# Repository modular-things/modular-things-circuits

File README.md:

# modular-things-circuits

Hardware repo for [modular-things](https://github.com/modular-things/modular-things/) custom circuits. Each folder includes a shematic image, board image, and relevant design files in a Fusion 360 Archive. 

`/samd21` contains the OG modular-things circuits based on the ATSAMD21E18A  

`/xiao` contains newer designs based on the seeed xiao development boards, in particular the RP2040 version  

`/backpacks` contain modular PHY add-ons, in development  

`/jewel` contains the stub of a usb-power-delivery based xiao-like module we are ~ planning  

To design a new board, you can start with the [base design for samd21s](samd21/base) or the [base design for the xiao platform](xiao/base). 

Note that it is also possible to virtualize *almost any existing arduino project* as a modular-thing - these circuits are just a cohesive, demonstrative set.

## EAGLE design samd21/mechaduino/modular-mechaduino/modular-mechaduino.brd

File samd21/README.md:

## atsamd21 based modular-things circuits

---

| accelerometer | |
| --- | --- |
|  |  |

| part | count | info ? |
| --- | --- | --- |
| ATSAMD21 | 1 | uc |
| JTAG 10-pin | 1 |
| VREG | 1 | 
| LSM6DSO Accelerometer | 1 |
| 0R 1206 | 1 |
| 1k 1206 | 1 |
| 2k2 1206 | 2 |
| 10k 1206 | 1 |
| 0.1uF 1206 | 2 |
| 1uF 1206 | 2 |
| 10uF 1206 | 2 |

---

| breadboard | |
| --- | --- |
|  |  |

| part | count | info ? |
| --- | --- | --- |
| ATSAMD21 | 1 | uc |
| JTAG 10-pin | 1 |
| VREG (big) | 1 | 
| 0R 1206 | 1 |
| 10k 1206 | 1 |
| 1uF 1206 | 2 |
| 10uF 1206 | 2 |

---

| capacitive | |
| --- | --- |
|  |  |

| part | count | info ? |
| --- | --- | --- |
| ATSAMD21 | 1 | uc |
| JTAG 10-pin | 1 |
| VREG | 1 | 
| 0R 1206 | 1 |
| 1k 1206 | 3 |
| 10k 1206 | 1 |
| 1uF 1206 | 2 |
| 10uF 1206 | 2 |

---

| low-fet | |
| --- | --- |
|  |  |

| part | count | info ? |
| --- | --- | --- |
| ATSAMD21 | 1 | uc |
| JTAG 10-pin | 1 |
| VREG | 1 | 
| NMOS | 1 |
| 2x3 SMT Header | 1 |
| 2x4 SMT Header | 1 |
| 0R 1206 | 2 |
| 1k 1206 | 2 |
| 10k 1206 | 1 |
| 1uF 1206 | 2 |
| 10uF 1206 | 2 |

---

| oled | |
| --- | --- |
|  |  |

`note: an early version of these circuits need SCL and SDA to be flipped in between the board and the OLED module`

| part | count | info ? |
| --- | --- | --- |
| ATSAMD21 | 1 | uc |
| JTAG 10-pin | 1 |
| VREG | 1 | 
| OLED Module | 1 |
| 0R 1206 | 1 |
| 4.99k 1206 | 2 |
| 10k 1206 | 1 |
| 1uF 1206 | 2 |
| 10uF 1206 | 2 |

---

| potentiometer | |
| --- | --- |
|  |  |

| part | count | info ? |
| --- | --- | --- |
| ATSAMD21 | 1 | uc |
| JTAG 10-pin | 1 |
| VREG | 1 | 
| POTS | 2 |
| 0R 1206 | 1 |
| 10k 1206 | 1 |
| 1uF 1206 | 2 |
| 10uF 1206 | 2 |

---

| rgbb | |
| --- | --- |
|  |  |

| part | count | info ? |
| --- | --- | --- |
| ATSAMD21 | 1 | uc |
| JTAG 10-pin | 1 |
| VREG | 1 | 
| RGB LED | 1 |
| SWTCH | 1 |
| 1x3 SMT Header | 1 |
| 0R 1206 | 1 |
| 1k 1206 | 3 |
| 10k 1206 | 2 |
| 1uF 1206 | 2 |
| 10uF 1206 | 2 |

---

| servo | |
| --- | --- |
|  |  |

| part | count | info ? |
| --- | --- | --- |
| ATSAMD21 | 1 | uc |
| JTAG 10-pin | 1 |
| VREG | 1 | 
| 1x3 SMT Header | 1 |
| 0R 1206 | 1 |
| 10k 1206 | 1 |
| 1uF 1206 | 1 |
| 10uF 1206 | 3 |

---

| stepper-hbridge | |
| --- | --- |
|  |  |

| part | count | info ? |
| --- | --- | --- |
| ATSAMD21 | 1 | uc |
| JTAG 10-pin | 1 |
| VREG | 1 | 
| H-Bridge | 2 |
| 2x3 SMT Header | 1 |
| 0R 1206 | 2 |
| 120R | 2 |
| Shunt | 2 | use ~ 300mOhm, we think |
| 10k 1206 | 1 |
| 0.1uF 1206 | 2 |
| 1uF 1206 | 4 |
| 10uF 1206 | 4 |

---

| sneaky mechaduino clone | |
| --- | --- |
|  |  |

In the style of the xiao boards (hole spacing / sizewise / PHY breakout wise) but w/ xiao! 

| part | count | info ? |
| --- | --- | --- |
| ATSAMD21 | 1 | uc |
| JTAG 10-pin | 1 |
| VREG | 1 | 
| H-Bridge | 2 |
| Shunt | 2 | use ~ 300mOhm, we think |
| 120R | 2 |
| 5k1 1206 | 2 |
| 10k 1206 | 1 |
| 0.1uF 1206 | 3 |
| 1uF 1206 | 4 |
| 10uF 1206 | 4 |

---

| time-of-flight | |
| --- | --- |
|  |  |

| part | count | info ? |
| --- | --- | --- |
| ATSAMD21 | 1 | uc |
| JTAG 10-pin | 1 |
| VREG | 1 | 
| VL53 TOF | 1 |
| 0R 1206 | 1 |
| 4.99k 1206 | 2 |
| 10k 1206 | 1 |
| 0.1uF 1206 | 1 |
| 1uF 1206 | 2 |
| 10uF 1206 | 2 |

---

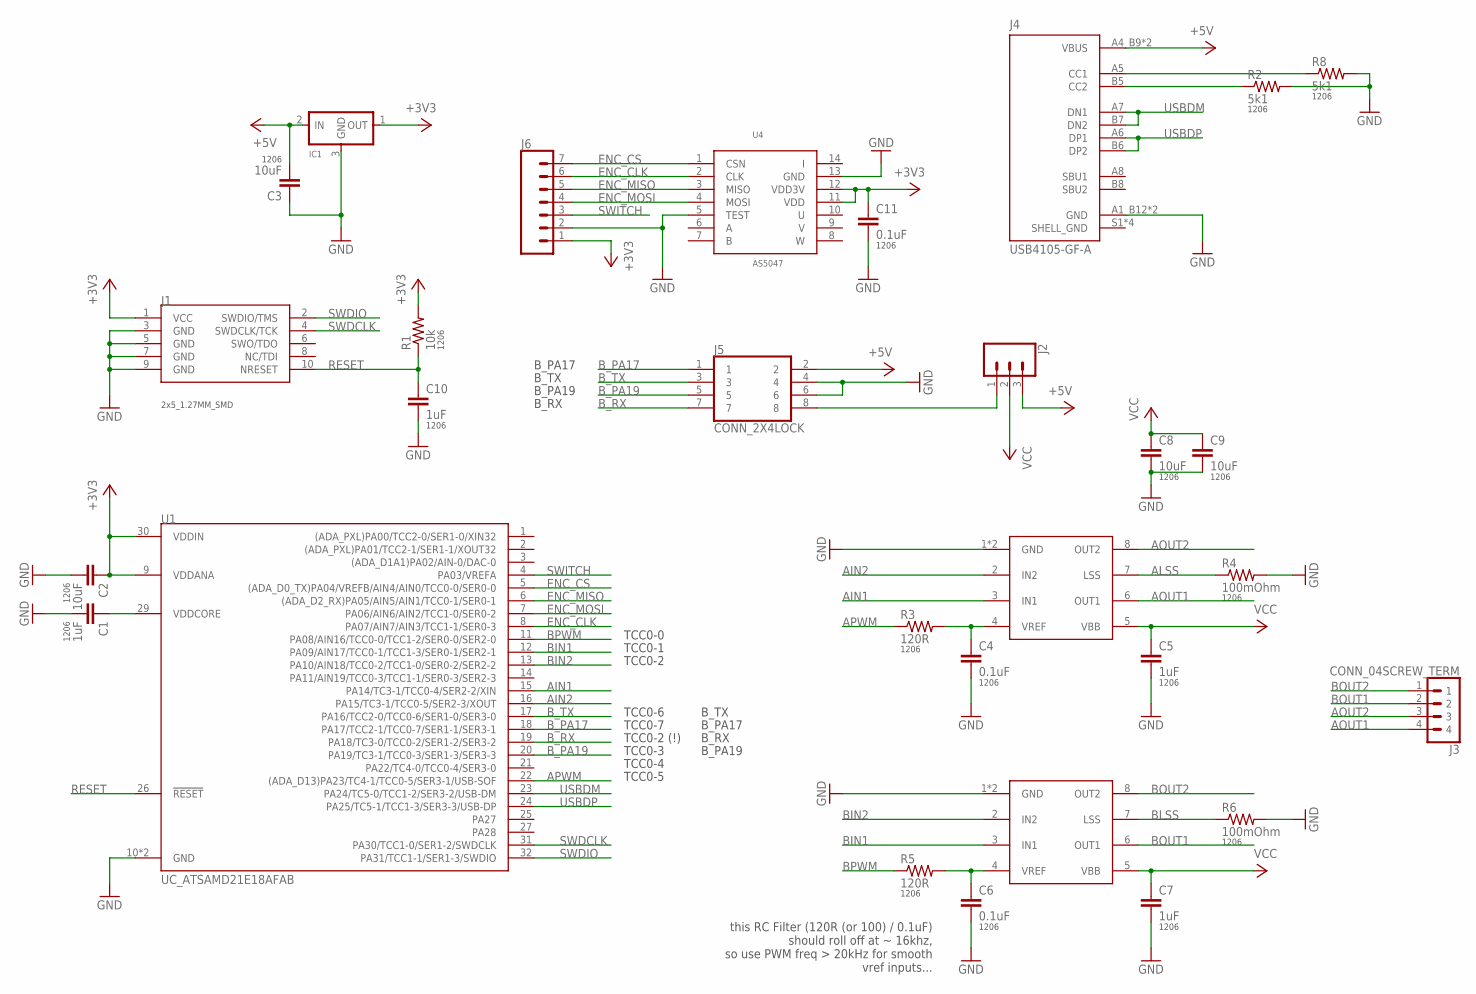
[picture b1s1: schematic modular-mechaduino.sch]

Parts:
C1, C5, C7, C10: 1uF; 1206
C2, C3, C8, C9: 10uF; 1206
C4, C6, C11: 0.1uF; 1206
IC1: VR_REGULATOR-SOT23SOT23; SOT23
J1: CONN_05X2_ARM_DEBUGSMD; 2X5_1.27MM_SMD
J2: CONN_03LOCK_NO_SILK; 1X03_LOCK_NO_SILK
J3: CONN_04SCREW_TERM; 1X04_SCREW-TERM
J4: USB4105-GF-A; GCT_USB4105-GF-A
J5: CONN_2X4LOCK; 2X4-LOCK
J6: CONN_07NO_SILK; 1X07_NO_SILK
R1: 10k; 1206
R2, R8: 5k1; 1206
R3, R5: 120R; 1206
R4, R6: 100mOhm; 1206
U1: UC_ATSAMD21E18AFAB; TQFP-32-FAB
U2, U3: A4950; SOIC8_PAD
U4: AS5047; TSSOP14

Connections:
+3V3: C2.1, C11.1, IC1.1 (OUT), J1.1 (VCC), J6.1, R1.2, U1.9 (VDDANA), U1.30 (VDDIN), U4.11 (VDD), U4.12 (VDD3V)
+5V: C3.2, IC1.2 (IN), J2.3, J4.A4_B9 (VBUS), J4.B4_A9 (VBUS), J5.2
AIN1: U1.15 (PA14/TC3-1/TCC0-4/SER2-2/XIN), U2.3 (IN1)
AIN2: U1.16 (PA15/TC3-1/TCC0-5/SER2-3/XOUT), U2.2 (IN2)
ALSS: R4.1, U2.7 (LSS)
AOUT1: J3.4, U2.6 (OUT1)
AOUT2: J3.3, U2.8 (OUT2)
APWM: R3.1, U1.22 ((ADA_D13)PA23/TC4-1/TCC0-5/SER3-1/USB-S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)
BIN1: U1.12 (PA09/AIN17/TCC0-1/TCC1-3/SER0-1/SER2-1), U3.3 (IN1)
BIN2: U1.13 (PA10/AIN18/TCC0-2/TCC1-0/SER0-2/SER2-2), U3.2 (IN2)
BLSS: R6.1, U3.7 (LSS)
BOUT1: J3.2, U3.6 (OUT1)
BOUT2: J3.1, U3.8 (OUT2)
BPWM: R5.1, U1.11 (PA08/AIN16/TCC0-0/TCC1-2/SER0-0/SER2-0)
B_PA17: J5.1, U1.18 (PA17/TCC2-1/TCC0-7/SER1-1/SER3-1)
B_PA19: J5.5, U1.20 (PA19/TC3-1/TCC0-3/SER1-3/SER3-3)
B_RX: J5.7, U1.19 (PA18/TC3-0/TCC0-2/SER1-2/SER3-2)
B_TX: J5.3, U1.17 (PA16/TCC2-0/TCC0-6/SER1-0/SER3-0)
ENC_CLK: J6.6, U1.8 (PA07/AIN7/AIN3/TCC1-1/SER0-3), U4.2 (CLK)
ENC_CS: J6.7, U1.5 ((ADA_D0_TX)PA04/VREFB/AIN4/AIN0/TCC0-0/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), U4.1 (CSN)
ENC_MISO: J6.5, U1.6 ((ADA_D2_RX)PA05/AIN5/AIN1/TCC0-1/SER0-1), U4.3 (MISO)
ENC_MOSI: J6.4, U1.7 (PA06/AIN6/AIN2/TCC1-0/SER0-2), U4.4 (MOSI)
GND: C1.2, C2.2, C3.1, C4.2, C5.2, C6.2, C7.2, C8.2, C9.2, C10.2, C11.2, IC1.3 (GND), J1.3 (GND), J1.5 (GND), J1.7 (GND), J1.9 (GND), J4.A1_B12 (GND), J4.B1_A12 (GND), J5.4, J5.6, J6.2, R2.2, R4.2, R6.2, R8.2, U1.10 (GND), U1.28 (GND), U2.1 (GND), U2.P$1 (GND), U3.1 (GND), U3.P$1 (GND), U4.5 (TEST), U4.13 (GND)
unnamed: C1.1, U1.29 (VDDCORE)
unnamed: C4.1, R3.2, U2.4 (VREF)
unnamed: J4.B5 (CC2), R2.1
unnamed: J4.A5 (CC1), R8.1
unnamed: C6.1, R5.2, U3.4 (VREF)
unnamed: J2.1, J5.8
RESET: C10.1, J1.10 (NRESET), R1.1, U1.26 (!RESET)
SHELL_GND: J4.S1 (SHELL_GND), J4.S2 (SHELL_GND), J4.S3 (SHELL_GND), J4.S4 (SHELL_GND)
SWDCLK: J1.4 (SWDCLK/TCK), U1.31 (PA30/TCC1-0/SER1-2/SWDCLK)
SWDIO: J1.2 (SWDIO/TMS), U1.32 (PA31/TCC1-1/SER1-3/SWDIO)
SWITCH: J6.3, U1.4 (PA03/VREFA)
USBDM: J4.A7 (DN1), J4.B7 (DN2), U1.23 (PA24/TC5-0/TCC1-2/SER3-2/USB-DM)
USBDP: J4.A6 (DP1), J4.B6 (DP2), U1.24 (PA25/TC5-1/TCC1-3/SER3-3/USB-DP)
VCC: C5.1, C7.1, C8.1, C9.1, J2.2, U2.5 (VBB), U3.5 (VBB)

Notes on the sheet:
TCC0-0
TCC0-1
TCC0-2
TCC0-3
TCC0-4
TCC0-5
TCC0-2 (!)
TCC0-7
TCC0-6
this RC Filter (120R (or 100) / 0.1uF) should roll off at ~ 16khz, so use PWM freq > 20kHz for smooth vref inputs...
B_PA17
B_TX
B_PA19
B_RX

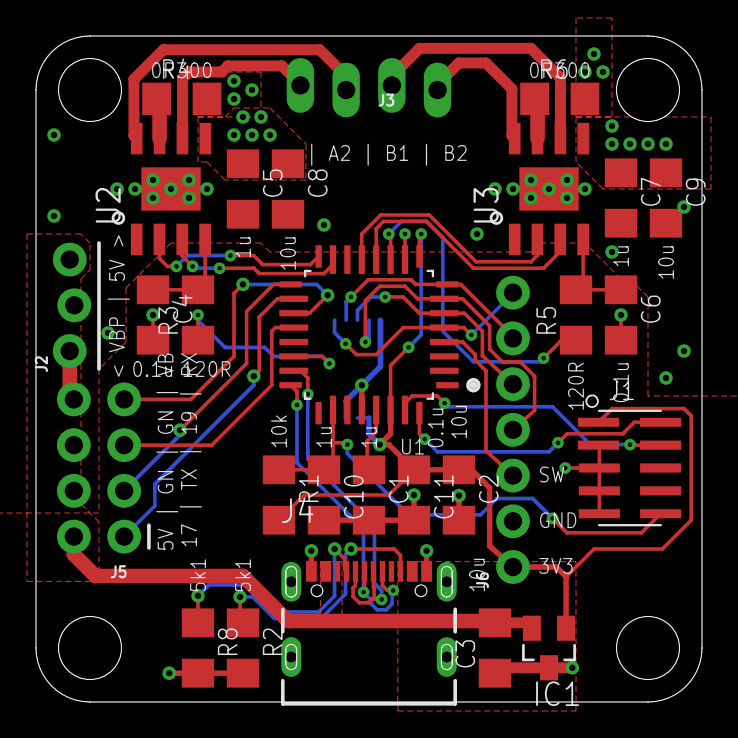
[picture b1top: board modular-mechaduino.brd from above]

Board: 4 copper layers, 37.0 x 37.0 mm, 29 parts (1 on the bottom side), 37 nets.

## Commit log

2022-11-10 hello things
2022-11-11 all circuits 2 fab
2022-11-22 pretty readme, with BOM notes
2022-11-22 upd8 oled
2022-11-30 add design files, some notes
2023-01-06 big cleanup, add xiao circuits and one backpack
2023-01-25 modular-mechaduino
2023-02-01 unfk tmc2209
2023-02-21 BOM notes on new steppers
2023-03-27 rouded xiao hbridge corners
2023-04-19 add pd hub, new hbridge stepper, rs485 backpack, and mounts
2023-04-19 adding usb pd imgs, design file
2023-04-20 add backpack mount
2023-04-21 mount v2
2023-06-22 MIDI io
2023-06-22 rename MIDI io files
2023-06-22 pin numbers
2023-06-23 pd hubs differentiated, rm mechaduino ref, add some bus backpacks
2023-11-07 4 new xiao things
2023-11-08 xiao button and BNO08x
2023-11-08 typo
2023-11-08 preview
2023-11-08 servo
2023-11-08 preview img

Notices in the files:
parts and their libraries:
SparkFun-Connectors: Licensing: Creative Commons ShareAlike 4.0 International - https://creativecommons.org/licenses/by-sa/4.0
